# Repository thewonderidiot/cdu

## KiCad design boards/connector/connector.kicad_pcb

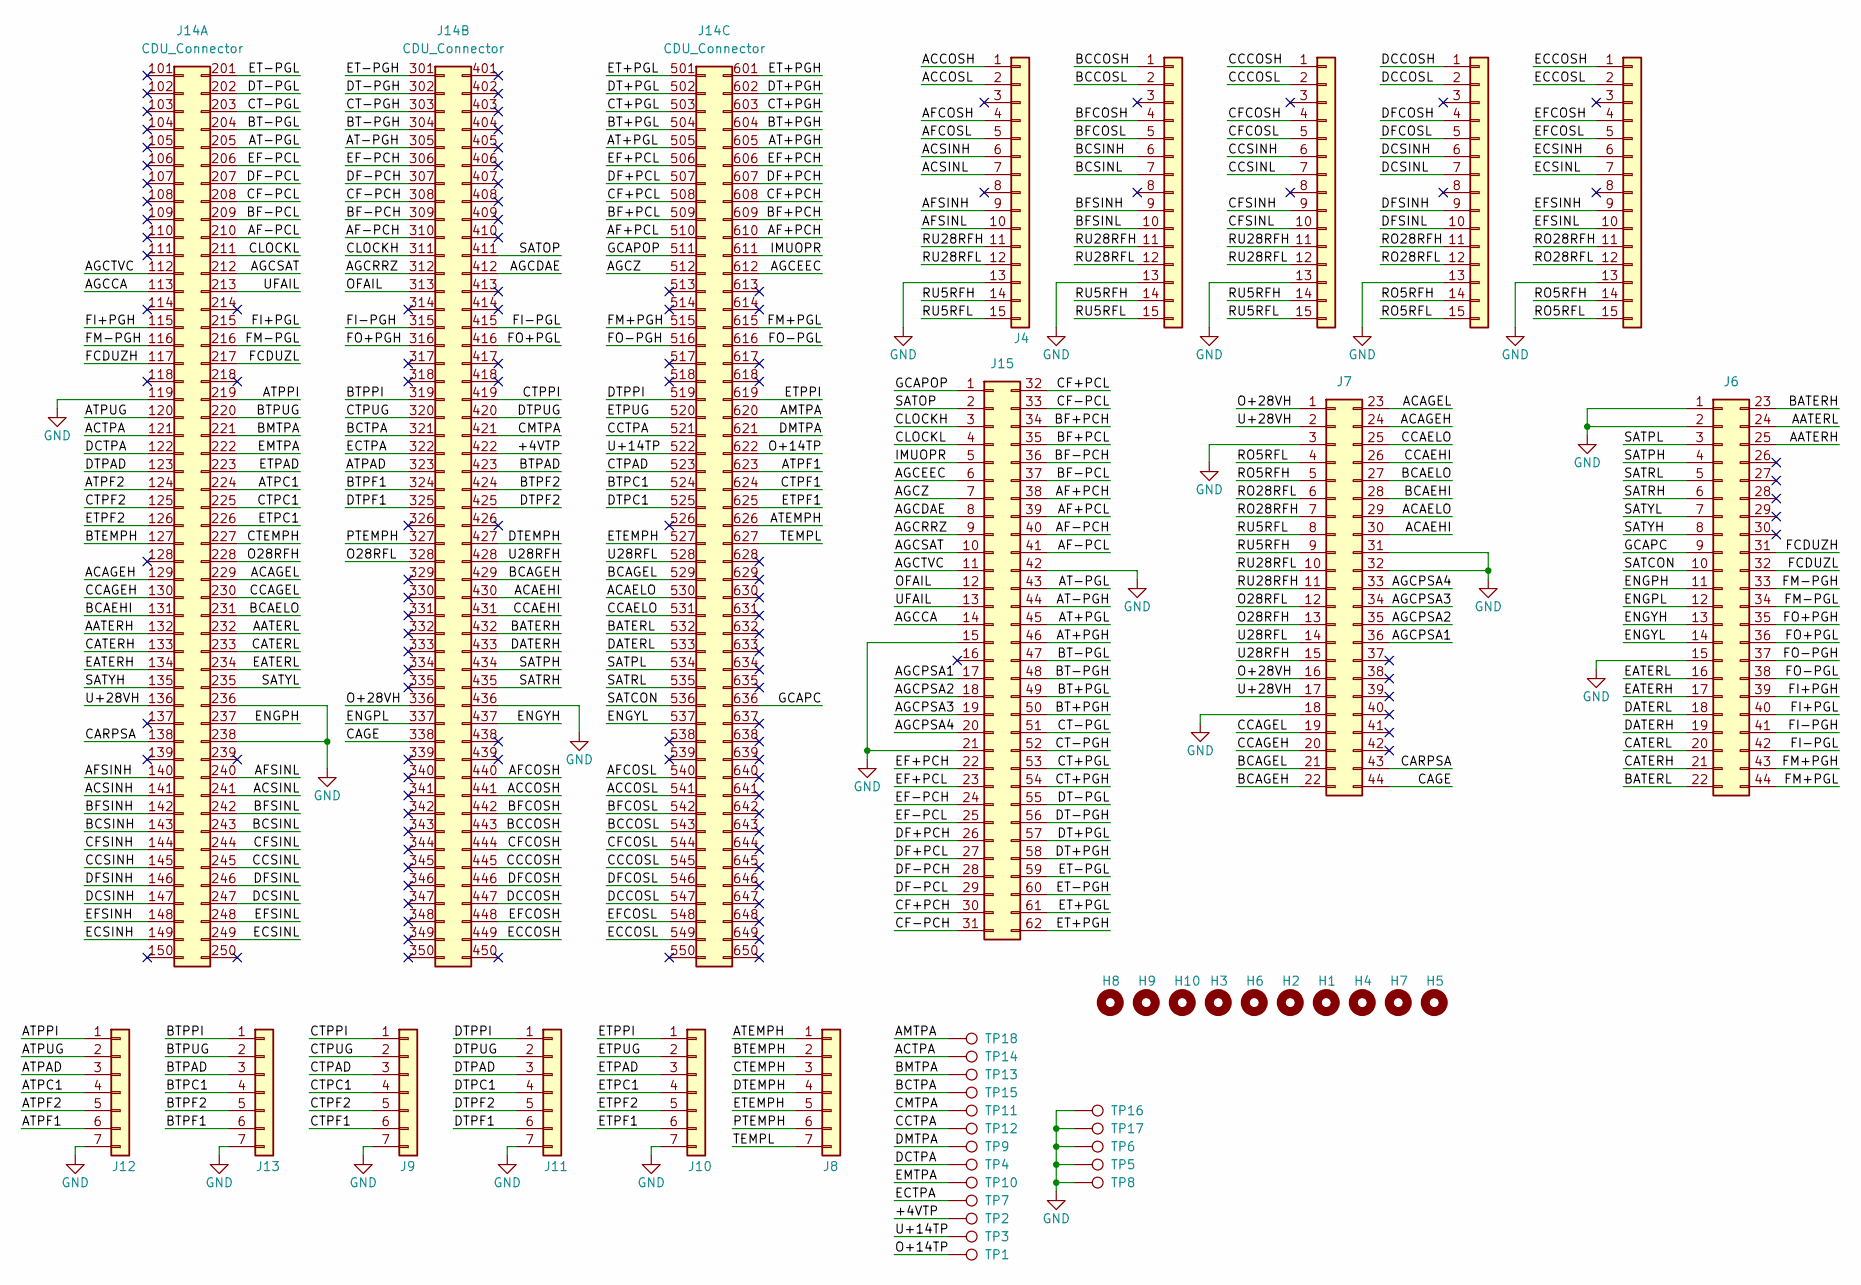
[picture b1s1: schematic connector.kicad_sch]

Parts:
H1, H2, H3, H4, H5, H6, H7, H8, H9, H10: MountingHole; MountingHole_4-40
J1, J2, J3, J4, J5: Conn_01x15; DSUB-15-HD_Female_Vertical_P2.29x1.98mm_MountingHoles
J6: Conn_02x22_Top_Bottom; DSUB-44-HD_Female_Vertical_P2.29x1.98mm_MountingHoles
J7: Conn_02x22_Top_Bottom; DSUB-44-HD_Male_Vertical_P2.29x1.98mm_MountingHoles
J8, J9, J10, J11, J12, J13: Conn_01x07; PinHeader_1x07_P2.54mm_Vertical
J14: CDU_Connector
J15: Conn_02x31_Top_Bottom; DSUB-62-HD_Female_Vertical_P2.41x1.98mm_MountingHoles
TP1, TP2, TP3, TP4, TP5, TP6, TP7, TP8, TP9, TP10, TP11, TP12, TP13, TP14, TP15, TP16, TP17, TP18: TestPoint; TestPoint_Keystone_5000-5004_Miniature

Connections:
/+4VTP: J14.422, TP2.1
/AATERH: J6.25, J14.132
/AATERL: J6.24, J14.232
/ACAEHI: J7.30, J14.430
/ACAELO: J7.29, J14.530
/ACAGEH: J7.24, J14.129
/ACAGEL: J7.23, J14.229
/ACCOSH: J4.1, J14.441
/ACCOSL: J4.2, J14.541
/ACSINH: J4.6, J14.141
/ACSINL: J4.7, J14.241
/ACTPA: J14.121, TP14.1
/AF+PCH: J14.610, J15.38
/AF+PCL: J14.510, J15.39
/AF-PCH: J14.310, J15.40
/AF-PCL: J14.210, J15.41
/AFCOSH: J4.4, J14.440
/AFCOSL: J4.5, J14.540
/AFSINH: J4.9, J14.140
/AFSINL: J4.10, J14.240
/AGCCA: J14.113, J15.14
/AGCDAE: J14.412, J15.8
/AGCEEC: J14.612, J15.6
/AGCPSA1: J7.36, J15.17
/AGCPSA2: J7.35, J15.18
/AGCPSA3: J7.34, J15.19
/AGCPSA4: J7.33, J15.20
/AGCRRZ: J14.312, J15.9
/AGCSAT: J14.212, J15.10
/AGCTVC: J14.112, J15.11
/AGCZ: J14.512, J15.7
/AMTPA: J14.620, TP18.1
/AT+PGH: J14.605, J15.46
/AT+PGL: J14.505, J15.45
/AT-PGH: J14.305, J15.44
/AT-PGL: J14.205, J15.43
/ATEMPH: J8.1, J14.626
/ATPAD: J12.3, J14.323
/ATPC1: J12.4, J14.224
/ATPF1: J12.6, J14.623
/ATPF2: J12.5, J14.124
/ATPPI: J12.1, J14.219
/ATPUG: J12.2, J14.120
/BATERH: J6.23, J14.432
/BATERL: J6.22, J14.532
/BCAEHI: J7.28, J14.131
/BCAELO: J7.27, J14.231
/BCAGEH: J7.22, J14.429
/BCAGEL: J7.21, J14.529
/BCCOSH: J5.1, J14.443
/BCCOSL: J5.2, J14.543
/BCSINH: J5.6, J14.143
/BCSINL: J5.7, J14.243
/BCTPA: J14.321, TP15.1
/BF+PCH: J14.609, J15.34
/BF+PCL: J14.509, J15.35
/BF-PCH: J14.309, J15.36
/BF-PCL: J14.209, J15.37
/BFCOSH: J5.4, J14.442
/BFCOSL: J5.5, J14.542
/BFSINH: J5.9, J14.142
/BFSINL: J5.10, J14.242
/BMTPA: J14.221, TP13.1
/BT+PGH: J14.604, J15.50
/BT+PGL: J14.504, J15.49
/BT-PGH: J14.304, J15.48
/BT-PGL: J14.204, J15.47
/BTEMPH: J8.2, J14.127
/BTPAD: J13.3, J14.423
/BTPC1: J13.4, J14.524
/BTPF1: J13.6, J14.324
/BTPF2: J13.5, J14.424
/BTPPI: J13.1, J14.319
/BTPUG: J13.2, J14.220
/CAGE: J7.44, J14.338
/CARPSA: J7.43, J14.138
/CATERH: J6.21, J14.133
/CATERL: J6.20, J14.233
/CCAEHI: J7.26, J14.431
/CCAELO: J7.25, J14.531
/CCAGEH: J7.20, J14.130
/CCAGEL: J7.19, J14.230
/CCCOSH: J3.1, J14.445
/CCCOSL: J3.2, J14.545
/CCSINH: J3.6, J14.145
/CCSINL: J3.7, J14.245
/CCTPA: J14.521, TP12.1
/CF+PCH: J14.608, J15.30
/CF+PCL: J14.508, J15.32
/CF-PCH: J14.308, J15.31
/CF-PCL: J14.208, J15.33
/CFCOSH: J3.4, J14.444
/CFCOSL: J3.5, J14.544
/CFSINH: J3.9, J14.144
/CFSINL: J3.10, J14.244
/CLOCKH: J14.311, J15.3
/CLOCKL: J14.211, J15.4
/CMTPA: J14.421, TP11.1
/CT+PGH: J14.603, J15.54
/CT+PGL: J14.503, J15.53
/CT-PGH: J14.303, J15.52
/CT-PGL: J14.203, J15.51
/CTEMPH: J8.3, J14.227
/CTPAD: J9.3, J14.523
/CTPC1: J9.4, J14.225
/CTPF1: J9.6, J14.624
/CTPF2: J9.5, J14.125
/CTPPI: J9.1, J14.419
/CTPUG: J9.2, J14.320
/DATERH: J6.19, J14.433
/DATERL: J6.18, J14.533
/DCCOSH: J1.1, J14.447
/DCCOSL: J1.2, J14.547
/DCSINH: J1.6, J14.147
/DCSINL: J1.7, J14.247
/DCTPA: J14.122, TP4.1
/DF+PCH: J14.607, J15.26
/DF+PCL: J14.507, J15.27
/DF-PCH: J14.307, J15.28
/DF-PCL: J14.207, J15.29
/DFCOSH: J1.4, J14.446
/DFCOSL: J1.5, J14.546
/DFSINH: J1.9, J14.146
/DFSINL: J1.10, J14.246
/DMTPA: J14.621, TP9.1
/DT+PGH: J14.602, J15.58
/DT+PGL: J14.502, J15.57
/DT-PGH: J14.302, J15.56
/DT-PGL: J14.202, J15.55
/DTEMPH: J8.4, J14.427
/DTPAD: J11.3, J14.123
/DTPC1: J11.4, J14.525
/DTPF1: J11.6, J14.325
/DTPF2: J11.5, J14.425
/DTPPI: J11.1, J14.519
/DTPUG: J11.2, J14.420
/EATERH: J6.17, J14.134
/EATERL: J6.16, J14.234
/ECCOSH: J2.1, J14.449
/ECCOSL: J2.2, J14.549
/ECSINH: J2.6, J14.149
/ECSINL: J2.7, J14.249
/ECTPA: J14.322, TP7.1
/EF+PCH: J14.606, J15.22
/EF+PCL: J14.506, J15.23
/EF-PCH: J14.306, J15.24
/EF-PCL: J14.206, J15.25
/EFCOSH: J2.4, J14.448
/EFCOSL: J2.5, J14.548
/EFSINH: J2.9, J14.148
/EFSINL: J2.10, J14.248
/EMTPA: J14.222, TP10.1
/ENGPH: J6.11, J14.237
/ENGPL: J6.12, J14.337
/ENGYH: J6.13, J14.437
/ENGYL: J6.14, J14.537
/ET+PGH: J14.601, J15.62
/ET+PGL: J14.501, J15.61
/ET-PGH: J14.301, J15.60
/ET-PGL: J14.201, J15.59
/ETEMPH: J8.5, J14.527
/ETPAD: J10.3, J14.223
/ETPC1: J10.4, J14.226
/ETPF1: J10.6, J14.625
/ETPF2: J10.5, J14.126
/ETPPI: J10.1, J14.619
/ETPUG: J10.2, J14.520
/FCDUZH: J6.31, J14.117
/FCDUZL: J6.32, J14.217
/FI+PGH: J6.39, J14.115
/FI+PGL: J6.40, J14.215
/FI-PGH: J6.41, J14.315
/FI-PGL: J6.42, J14.415
/FM+PGH: J6.43, J14.515
/FM+PGL: J6.44, J14.615
/FM-PGH: J6.33, J14.116
/FM-PGL: J6.34, J14.216
/FO+PGH: J6.35, J14.316
/FO+PGL: J6.36, J14.416
/FO-PGH: J6.37, J14.516
/FO-PGL: J6.38, J14.616
/GCAPC: J6.9, J14.636
/GCAPOP: J14.511, J15.1
/IMUOPR: J14.611, J15.5
/O28RFH: J7.13, J14.228
/O28RFL: J7.12, J14.328
/O+14TP: J14.622, TP1.1
/O+28VH: J7.1, J7.16, J14.336
/OFAIL: J14.313, J15.12
/PTEMPH: J8.6, J14.327
/RO5RFH: J1.14, J2.14, J7.5
/RO5RFL: J1.15, J2.15, J7.4
/RO28RFH: J1.11, J2.11, J7.7
/RO28RFL: J1.12, J2.12, J7.6
/RU5RFH: J3.14, J4.14, J5.14, J7.9
/RU5RFL: J3.15, J4.15, J5.15, J7.8
/RU28RFH: J3.11, J4.11, J5.11, J7.11
/RU28RFL: J3.12, J4.12, J5.12, J7.10
/SATCON: J6.10, J14.536
/SATOP: J14.411, J15.2
/SATPH: J6.4, J14.434
/SATPL: J6.3, J14.534
/SATRH: J6.6, J14.435
/SATRL: J6.5, J14.535
/SATYH: J6.8, J14.135
/SATYL: J6.7, J14.235
/TEMPL: J8.7, J14.627
/U28RFH: J7.15, J14.428
/U28RFL: J7.14, J14.528
/U+14TP: J14.522, TP3.1
/U+28VH: J7.2, J7.17, J14.136
/UFAIL: J14.213, J15.13
GND: J1.13, J2.13, J3.13, J4.13, J5.13, J6.1, J6.2, J6.15, J7.3, J7.18, J7.31, J7.32, J9.7, J10.7, J11.7, J12.7, J13.7, J14.119, J14.236, J14.238, J14.436, J15.15, J15.21, J15.42, TP5.1, TP6.1, TP8.1, TP16.1, TP17.1

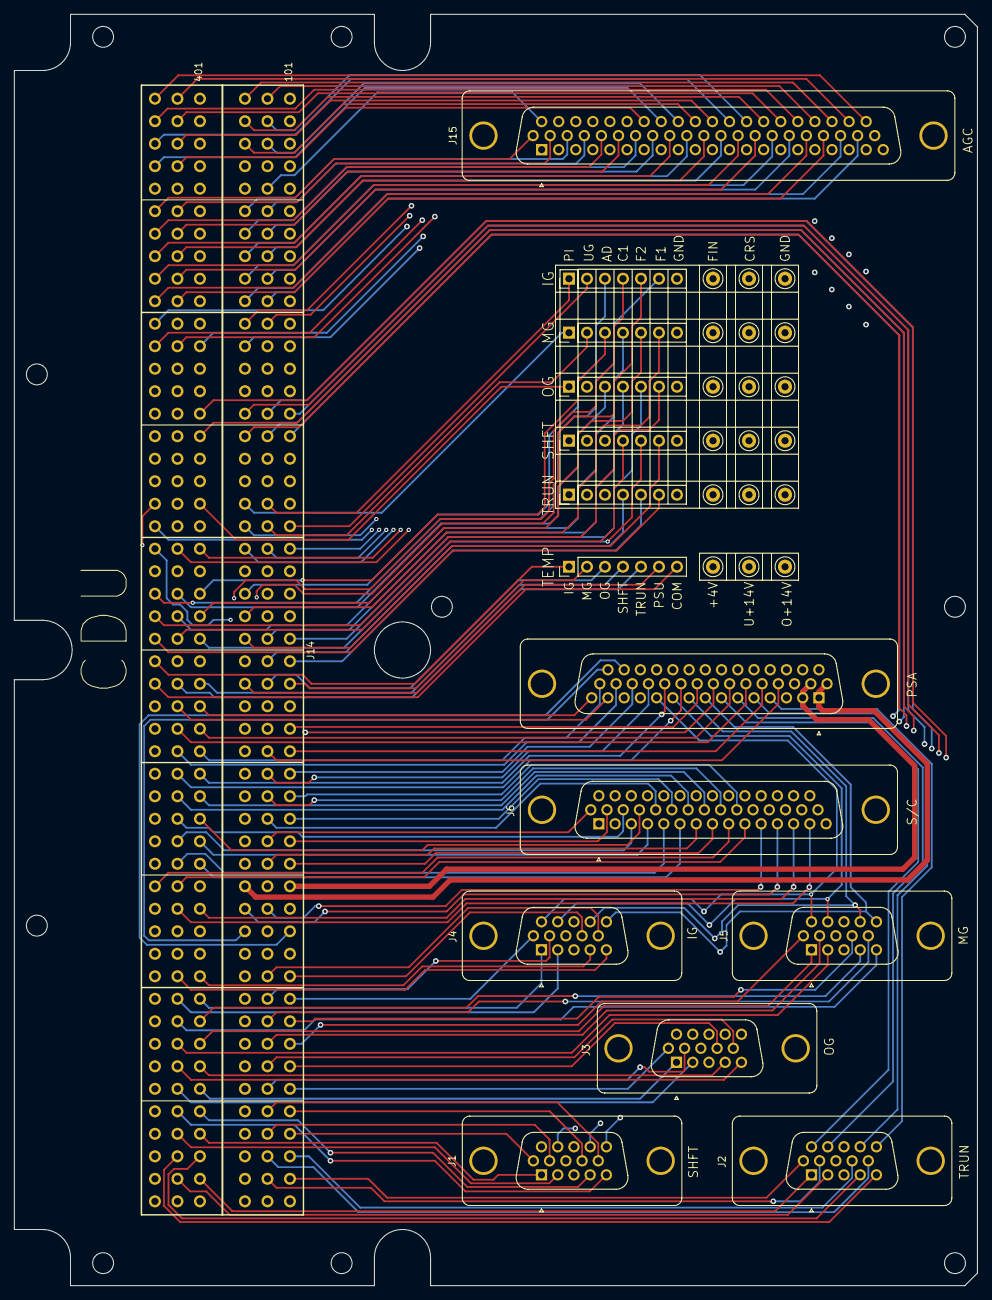
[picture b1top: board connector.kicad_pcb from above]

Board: 4 copper layers, 135.9 x 179.4 mm, 43 parts (0 on the bottom side), 213 nets.
